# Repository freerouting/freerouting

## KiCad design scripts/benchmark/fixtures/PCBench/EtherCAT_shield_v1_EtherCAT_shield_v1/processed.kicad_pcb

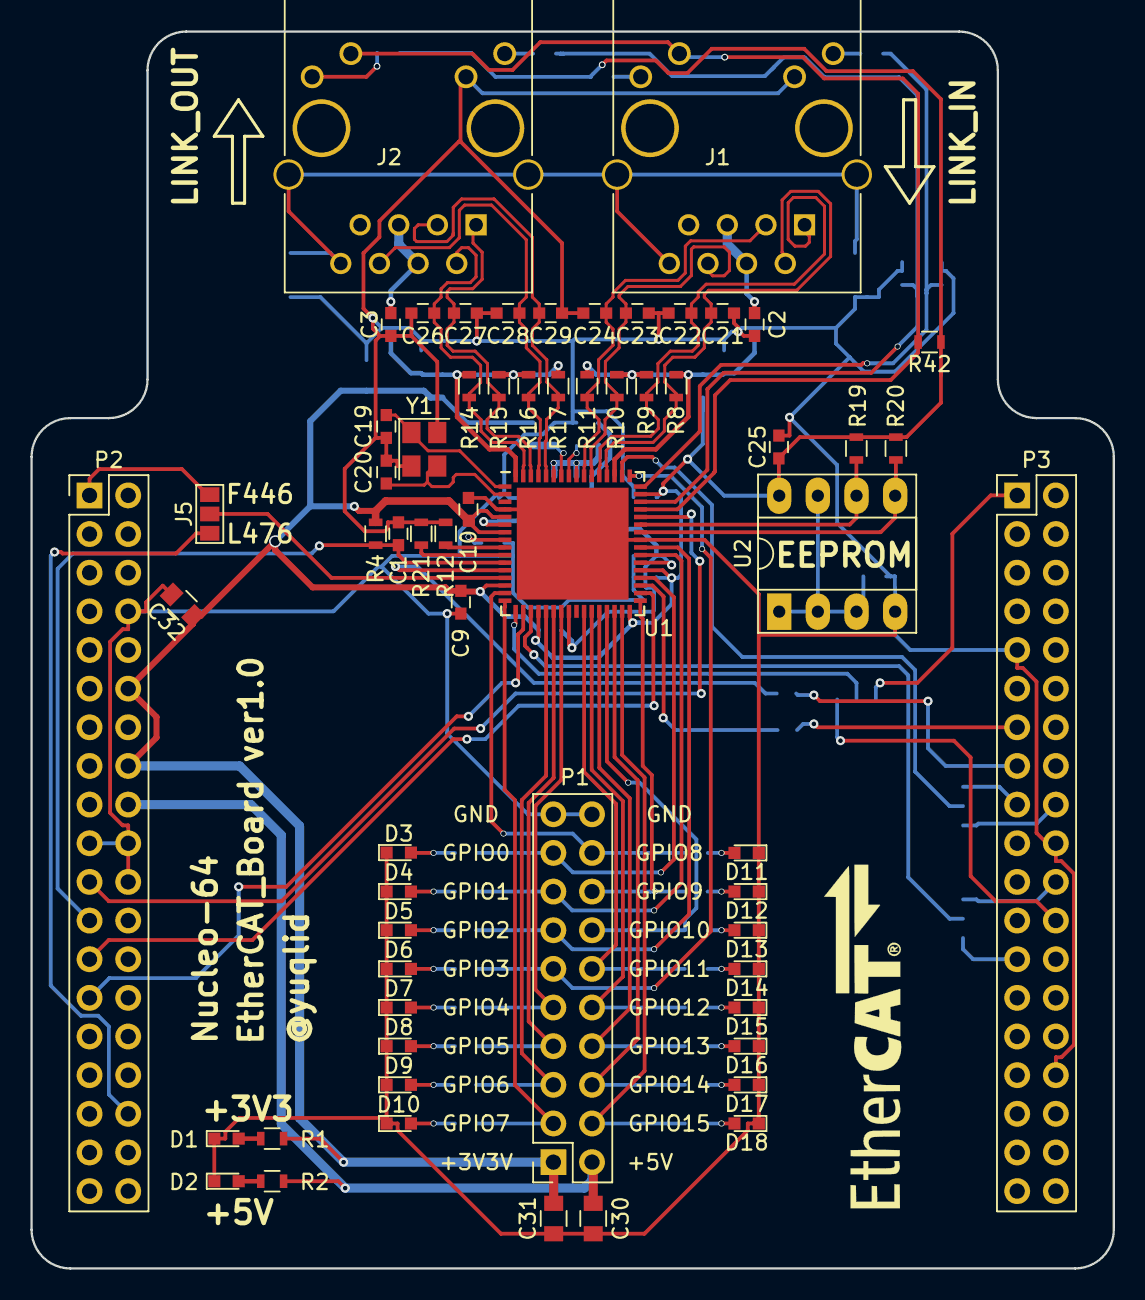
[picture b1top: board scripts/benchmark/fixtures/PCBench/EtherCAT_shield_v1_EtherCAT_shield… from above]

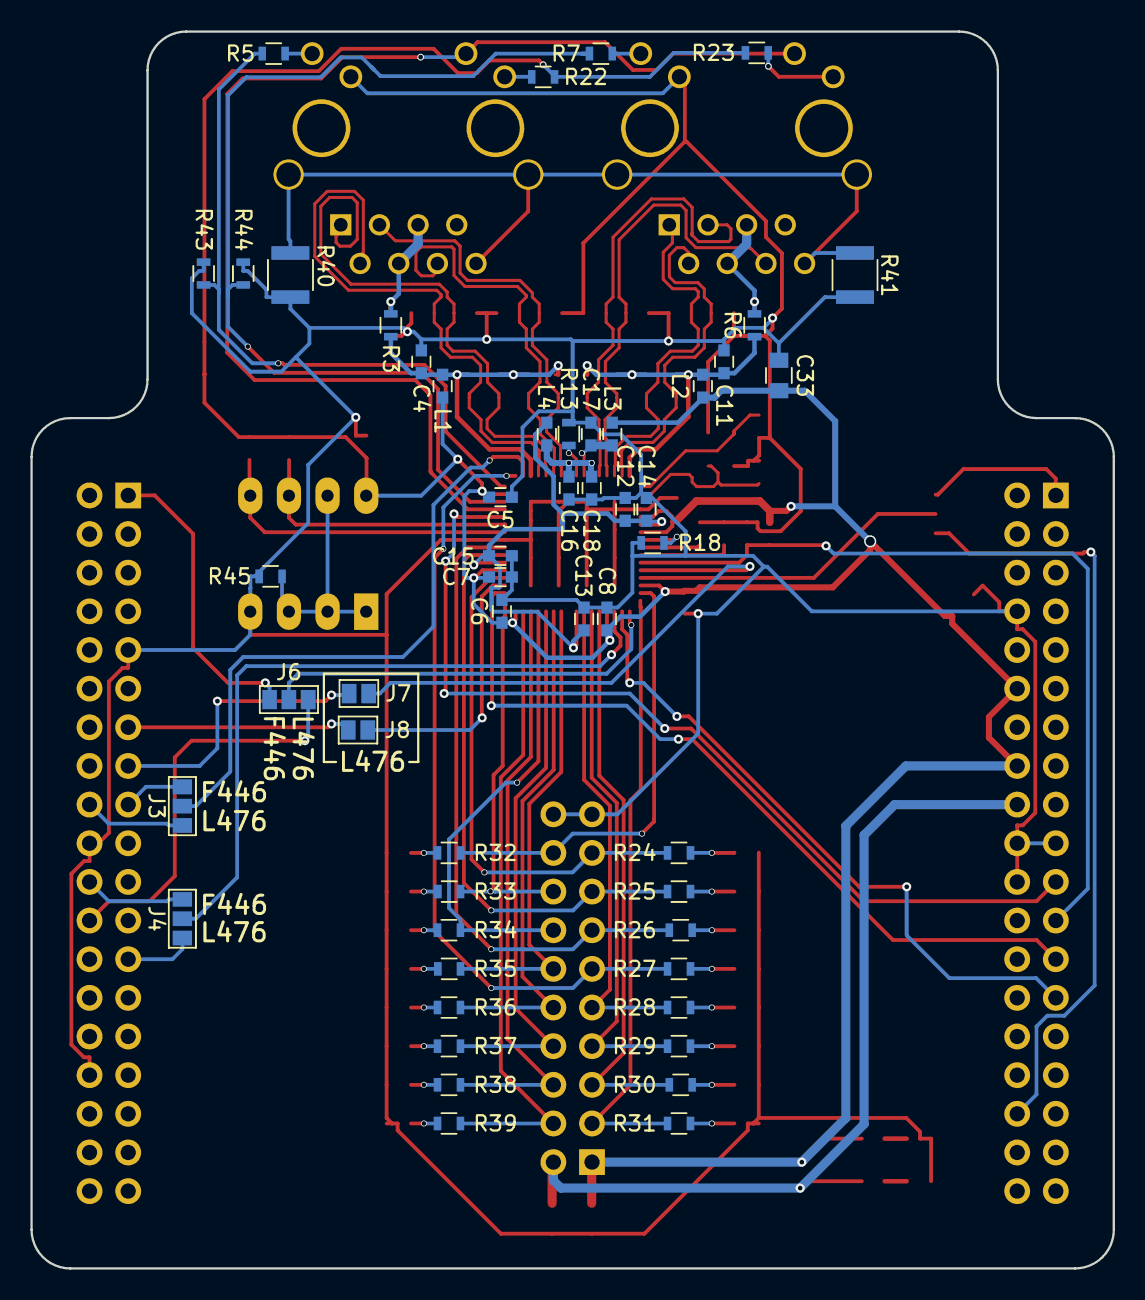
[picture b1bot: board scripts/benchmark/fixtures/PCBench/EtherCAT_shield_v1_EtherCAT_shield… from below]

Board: 2 copper layers, 71.1 x 81.3 mm, 114 parts (52 on the bottom side), 89 nets.

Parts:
C1, C4, C5, C6, C7, C8, C9, C10, C11, C14, C15, C16, C17, C18, C25: 0.1u; C_0603
C2, C3: 0.022u; C_0603
C12: 1u; C_0603
C13: 470p; C_0603
C19, C20: C; C_0603
C21, C22, C23, C24, C26, C27, C28, C29: 10p; C_0603
C30, C31, C32, C33: 10u; C_0805
D1, D2, D3, D4, D5, D6, D7, D8, D9, D10, D11, D12, D13, D14, D15, D16, D17, D18: LED; LED_0603
J1, J2: RJ45-PULSETRANS; RJ45_J0011D21BNL
J3, J4, J5, J6: GS3
J7, J8: GS2
L1, L2, L3, L4: L; C_0603
P1: CONN_02X10; Socket_Strip_Straight_2x10_Pitch2.54mm
P2, P3: CONN_02X19; Pin_Header_Straight_2x19_Pitch2.54mm
R1, R2: R; R_0603
R3, R6: 0; R_0603
R4, R12, R18, R21, R42, R43, R44: 10k; R_0603
R5, R7, R22, R23: 330; R_0603
R8, R9, R10, R11, R14, R15, R16, R17: 49.9; R_0603
R13: 12.1k; R_0603
R19, R20: 2k; R_0603
R24, R25, R26, R27, R28, R29, R30, R31, R32, R33, R34, R35, R36, R37, R38, R39: 1k; R_0603
R40, R41: R; R_1210
R45: 4.7k; R_0603
U1: LAN9252; QFN-64-1EP_9x9mm_Pitch0.5mm
U2: 24LC00; DIP-8_W7.62mm_Socket_LongPads
Y1: Crystal_GND24; Crystal_SMD_Abracon_ABM8G-4pin_3.2x2.5mm

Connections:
+3V3: C5.1, C6.1, C7.1, C8.1, C9.1, C10.1, C25.1, C31.1, C32.1, C33.1, L1.1, L2.1, L3.1, P1.1, P2.12, P2.16, R1.1, R4.1, R19.1, R20.1, R22.1, R23.1, R42.1, U1.5, U1.7, U1.14, U1.20, U1.32, U1.37, U1.47, U2.8
+5V: C30.1, P1.2, P2.18, R2.1
/LAN9252/LINKACTLED0: R5.1, R43.1, U1.48
/LAN9252/LINKACTLED1: R7.1, R44.1, U1.46
/LAN9252/RUNLED: J1.11, J2.11, R42.2, U1.45
/LAN9252/VDD33TXRX1: C4.1, L1.2, R3.2, R8.2, R9.2, R10.2, R11.2, U1.51
/LAN9252/VDDTXRX2: C11.1, L2.2, R6.1, R14.2, R15.2, R16.2, R17.2, U1.64
GND: C1.2, C2.2, C3.2, C4.2, C5.2, C6.2, C7.2, C8.2, C9.2, C10.2, C11.2, C12.2, C13.2, C14.2, C15.2, C16.2, C17.2, C18.2, C19.2, C20.2, C21.2, C22.2, C23.2, C24.2, C25.2, C26.2, C27.2, C28.2, C29.2, C30.2, C31.2, C32.2, C33.2, D1.1, D2.1, D3.1, D4.1, D5.1, D6.1, D7.1, D8.1, D9.1, D10.1, D11.1, D12.1, D13.1, D14.1, D15.1, D16.1, D17.1, D18.1, J1.10, J2.10, P1.19, P1.20, P2.8, P2.19, P2.20, P2.22, P3.9, P3.20, P3.32, R12.2, R13.2, R18.2, R21.2, R40.2, R41.2, R43.2, R44.2, R45.2, U1.4, U1.41, U1.65, U2.4, Y1.2, Y1.4
GNDPWR: J1.8, J1.13, J1.14, J2.8, J2.13, J2.14, R40.1, R41.1
GPIO0: P1.17, R24.2, U1.36
GPIO1: P1.15, R25.2, U1.39
GPIO2: P1.13, R26.2, U1.40
GPIO3: P1.11, R27.2, U1.49
GPIO4: P1.9, R28.2, U1.23
GPIO5: P1.7, R29.2, U1.22
GPIO6: P1.5, R30.2, U1.21
GPIO7: P1.3, R31.2, U1.16
GPIO8: P1.18, R32.2, U1.15
GPIO9: P1.16, R33.2, U1.33
GPIO10: P1.14, R34.2, U1.29
GPIO11: P1.12, R35.2, U1.26
GPIO12: P1.10, R36.2, U1.27
GPIO13: P1.8, R37.2, U1.28
GPIO14: P1.6, R38.2, U1.30
GPIO15: P1.4, R39.2, U1.31
LAN9252_IRQ: P2.21, U1.44
LAN9252_RST: C1.1, P2.23, R4.2, U1.11
unnamed: C2.1, J1.4, J1.5, R3.1
unnamed: C3.1, J2.4, J2.5, R6.2
unnamed: C12.1, C13.1, C14.1, C15.1, L4.1, U1.6, U1.24, U1.38
unnamed: C16.1, C18.1, L4.2, U1.56, U1.59
unnamed: C17.1, L3.2, U1.58
unnamed: C19.1, U1.1, Y1.1
unnamed: C20.1, U1.2, Y1.3
unnamed: D1.2, R1.2
unnamed: D2.2, R2.2
unnamed: D3.2, R24.1
unnamed: D4.2, R25.1
unnamed: D5.2, R26.1
unnamed: D6.2, R27.1
unnamed: D7.2, R28.1
unnamed: D8.2, R29.1
unnamed: D9.2, R30.1
unnamed: D10.2, R31.1
unnamed: D11.2, R32.1
unnamed: D12.2, R33.1
unnamed: D13.2, R34.1
unnamed: D14.2, R35.1
unnamed: D15.2, R36.1
unnamed: D16.2, R37.1
unnamed: D17.2, R38.1
unnamed: D18.2, R39.1
unnamed: J1.9, R5.2
unnamed: J1.12, R22.2
unnamed: J2.9, R7.2
unnamed: J2.12, R23.2
unnamed: R12.1, U1.9
unnamed: R13.1, U1.57
unnamed: R18.1, U1.8
unnamed: R19.2, U1.43, U2.6
unnamed: R20.2, U1.42, U2.5
unnamed: R21.1, U1.10
unnamed: R45.1, U2.1, U2.2, U2.3, U2.7
PA6: J8.2, P3.13
PA7: J7.2, P3.15
PB0: J5.3, P2.34
PB1: J6.3, P3.24
PB2: J4.1, P3.22
PB6: J3.1, P3.17
PB10: J4.3, P3.25
PB11: J3.3, P3.18
PC9: J6.1, P3.1
PC10: J5.1, P2.1
RX1_N: C23.1, J1.6, R10.1, U1.54
RX1_P: C24.1, J1.3, R11.1, U1.55
RX2_N: C28.1, J2.6, R16.1, U1.61
RX2_P: C29.1, J2.3, R17.1, U1.60
SCK: J4.2, U1.19
SIO0: J6.2, U1.17
SIO1: J5.2, U1.13
SIO2: J7.1, U1.12
SIO3: J8.1, U1.35
SYNC0: P2.25, U1.34
SYNC1: P2.27, U1.18
TX1_N: C21.1, J1.2, R8.1, U1.52
TX1_P: C22.1, J1.1, R9.1, U1.53
TX2_N: C26.1, J2.2, R14.1, U1.63
TX2_P: C27.1, J2.1, R15.1, U1.62
~SCS: J3.2, U1.50

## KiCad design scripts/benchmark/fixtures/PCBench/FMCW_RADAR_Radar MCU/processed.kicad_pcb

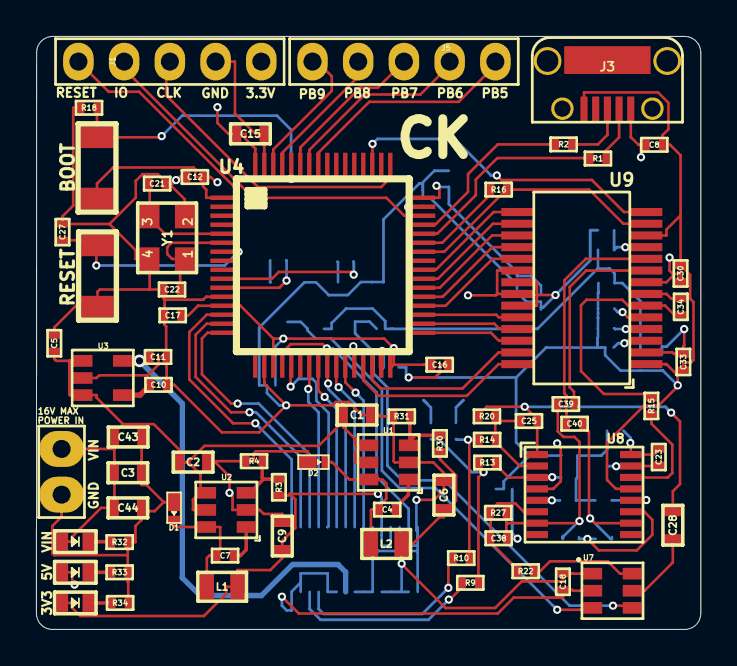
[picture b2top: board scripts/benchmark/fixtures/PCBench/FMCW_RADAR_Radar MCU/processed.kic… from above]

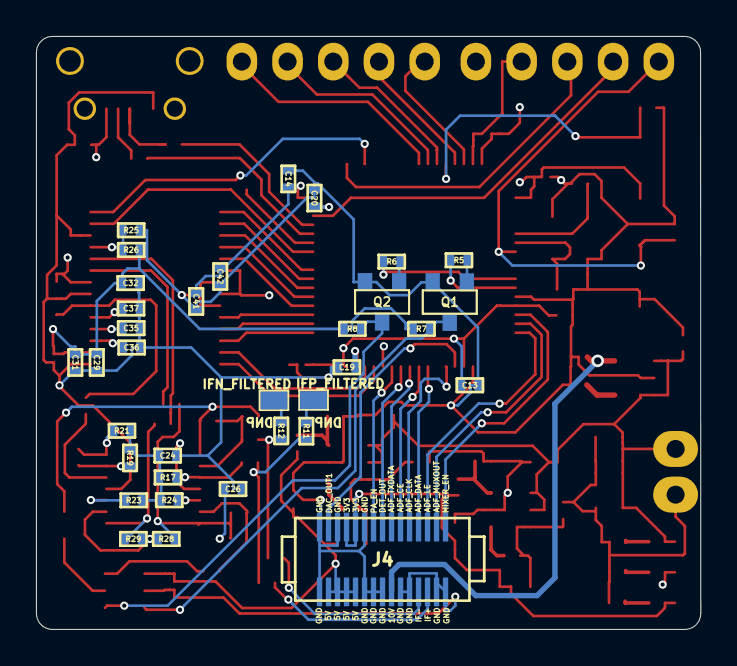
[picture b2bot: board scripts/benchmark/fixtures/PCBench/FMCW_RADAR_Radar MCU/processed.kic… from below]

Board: 4 copper layers, 36.9 x 32.9 mm, 104 parts (34 on the bottom side), 89 nets.

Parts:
3V3, 5V: Led_Diode; Diode_0603
BOOT: DFU_Button; Button_B3U_1000P
C1, C2, C15, C28: 10uF; SMD_0603
C3, C6, C9, C43, C44: 22uF; SMD_0603
C4, C7, C10: 10nF; SMD_0402
C5, C11, C16, C17, C19, C20, C29: 2.2uF; SMD_0402
C8, C12, C13, C14, C18, C23, C24, C26, C27, C30, C31, C34, C35, C36, C37, C41, C42: 100nF; SMD_0402
C21, C22: 15pF; SMD_0402
C25, C38: 33pF; SMD_0402
C32, C33: 100pF; SMD_0402
C39, C40: 1uF; SMD_0402
D1, D2: SDM2U30CSP_7; Diode_SDM2U30CSP_7
IFN_FILTERED: IF-; SolderPad_1_1.5mm_SMD_Rectangle
IFP_FILTERED: IF+; SolderPad_1_1.5mm_SMD_Rectangle
J1: SWD_DEBUGGER; PinHeader_1x5_P2.54mm
J3: USB_MicroB; USB_MicroB_TH
J4: Connector_02x15; PinHeader_2x15_DF12B(5.0)-30DP-0.5V(86)
J5: GPIO_EXTRA; PinHeader_1x5_P2.54mm
L1, L2: 4.7uH; SMD_0805
POWER IN: Connector_01x02; PinHeader_1x2_P2.54mm
Q1, Q2: BSS138; SOT23_3
R1, R2, R16: 22; SMD_0402
R3: 14.7K; SMD_0402
R4, R23, R27, R31: 4.7K; SMD_0402
R5, R6, R22: 100; SMD_0402
R7, R8, R17, R24, R28, R29: 10K; SMD_0402
R9, R10, R26: 0; SMD_0402
R11, R12, R25: DNP; SMD_0402
R13, R14, R18, R20, R32, R33, R34: 1K; SMD_0402
R15, R19: 2.49K; SMD_0402
R21: 49.9; SMD_0402
R30: 24.4K; SMD_0402
RESET: Reset_Button; Button_B3U_1000P
U1, U2: AP3211; SOT23_6
U3: LP2985_10; SOT23_5
U4: STM32F405; LQFP64_10x10mm_P0.5mm
U7: MCP4022_202; SOT23_6
U8: LT1817; SSOP16_3.9x4.9mm_P0.635mm
U9: MAX1426; SSOP28_5.3x10.2mm_P0.65mm
VIN: Led_Diode; Diode_0603
Y1: 8MHz; Crystal_3.2x2.5mm

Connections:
+3V3: 3V3.2, BOOT.2, C9.1, C12.1, C13.1, C14.1, C15.1, C16.1, C17.1, C41.2, C42.2, J1.1, J4.11, J4.12, L1.2, R3.1, U4.1, U4.13, U4.19, U4.32, U4.48, U4.64, U9.20, U9.22
+5V: 5V.2, C6.1, C8.1, C18.1, C26.1, C29.1, C30.1, C31.1, C32.1, C33.1, J3.1, J4.17, J4.18, J4.19, J4.20, L2.2, R7.1, R8.1, R26.2, R30.1, U7.1, U8.4, U9.2, U9.8
+10V: C11.1, J4.24, U3.5
+VBattery: C1.1, C2.1, C3.1, C5.2, C43.1, C44.1, POWER IN.2, U1.4, U1.5, U2.4, U2.5, U3.1, U3.3, VIN.2
ADC_CLK: R16.2, U4.42, U9.13
ADC_IN+: C39.1, U9.9
ADC_IN-: C40.1, U9.10
ADC_OE: U4.51, U9.14
ADF_CE: J4.6, U4.24
ADF_CLK: J4.5, U4.21
ADF_DATA: J4.4, U4.23
ADF_LE: J4.3, U4.16
ADF_MUXOUT: J4.2, U4.15
ADF_TXDATA: J4.7, U4.25
CML: C34.2, R15.1, U9.6
CMLP: R25.1, R26.1, U9.11
CM_BIAS: C24.2, R17.1, R19.2, R21.1, R23.2, R24.1
D0: U4.29, U9.28
D1: U4.30, U9.27
D2: U4.33, U9.26
D3: U4.34, U9.25
D4: U4.35, U9.24
D5: U4.36, U9.19
D6: U4.37, U9.18
D7: U4.38, U9.17
D8: U4.39, U9.16
D9: U4.40, U9.15
DAC_OUT1: J4.14, U4.20
DET_OUT: J4.8, U4.26
GND: C1.2, C2.2, C3.2, C5.1, C6.2, C8.2, C9.2, C10.1, C11.2, C12.2, C13.2, C14.2, C15.2, C16.2, C17.2, C18.2, C19.2, C20.2, C21.2, C22.2, C24.1, C26.2, C27.2, C29.2, C30.2, C31.2, C32.2, C33.2, C34.1, C35.2, C36.2, C37.2, C41.1, C42.1, C43.2, C44.2, D1.2, D2.2, J1.2, J3.5, J4.10, J4.13, J4.15, J4.16, J4.21, J4.22, J4.23, J4.25, J4.26, J4.29, J4.30, POWER IN.1, Q1.2, Q2.2, R4.2, R18.1, R25.2, R31.2, R32.2, R33.2, R34.2, RESET.2, U1.2, U2.2, U3.2, U4.12, U4.18, U4.28, U4.63, U7.2, U8.13, U9.1, U9.7, U9.12, U9.21, U9.23, Y1.2, Y1.4
IFN_Filtered: J4.27, R10.1
IFP_Filtered: J4.28, R9.1
MCP_AOUT: R22.1, U7.6
MCP_CS_3V3: R6.1, U4.10
MCP_UD_3V3: R5.1, U4.11
MCP_WIN: C28.1, U7.5
MCP_~CS~_5V: Q2.3, R8.2, U7.4
MCP_~UD~_5V: Q1.3, R7.2, U7.3
MIXER_ENB: J4.1, U4.14
unnamed: C4.1, U1.1
unnamed: C4.2, D2.1, L2.1, U1.6
unnamed: C7.1, U2.1
unnamed: C7.2, D1.1, L1.1, U2.6
unnamed: C10.2, U3.4
unnamed: C19.1, U4.31
unnamed: C20.1, U4.47
unnamed: C21.1, U4.5, Y1.3
unnamed: C22.1, U4.6, Y1.1
unnamed: C23.1, R21.2, U8.16
unnamed: C23.2, R19.1, U8.15
unnamed: C25.1, C28.2, R20.2, U8.1
unnamed: C25.2, R14.2, R20.1, U8.2
unnamed: C35.1, U9.4
unnamed: C36.1, U9.3
unnamed: C37.1, U9.5
unnamed: C38.1, C39.2, R27.2, R28.1, U8.7
unnamed: C38.2, R22.2, R27.1, U8.6
unnamed: C40.2, R29.2, U8.10
unnamed: R32.1, VIN.1
unnamed: 5V.1, R33.1
unnamed: 3V3.1, R34.1
unnamed: J3.2, R1.1
unnamed: J3.3, R2.1
unnamed: Q1.1, R5.2
unnamed: Q2.1, R6.2
unnamed: R3.2, R4.1, U2.3
unnamed: R10.2, R12.1, R14.1
unnamed: R9.2, R11.1, R13.1
unnamed: IFP_FILTERED.1, R11.2
unnamed: IFN_FILTERED.1, R12.2
unnamed: R13.2, R17.2, U8.3
unnamed: R15.2, U8.14
unnamed: R16.1, U4.43
unnamed: BOOT.1, R18.2, U4.60
unnamed: R23.1, U8.12
unnamed: R24.2, U8.5
unnamed: R28.2, R29.1, U8.11
unnamed: R30.2, R31.1, U1.3
PA_EN: J4.9, U4.27
PB5: J5.1, U4.57
PB6: J5.2, U4.58
PB7: J5.3, U4.59
PB8: J5.4, U4.61
PB9: J5.5, U4.62
RESET: C27.1, J1.5, RESET.1, U4.7
SWDCLK: J1.3, U4.49
SWDIO: J1.4, U4.46
USB_D+: R2.2, U4.45
USB_D-: R1.2, U4.44

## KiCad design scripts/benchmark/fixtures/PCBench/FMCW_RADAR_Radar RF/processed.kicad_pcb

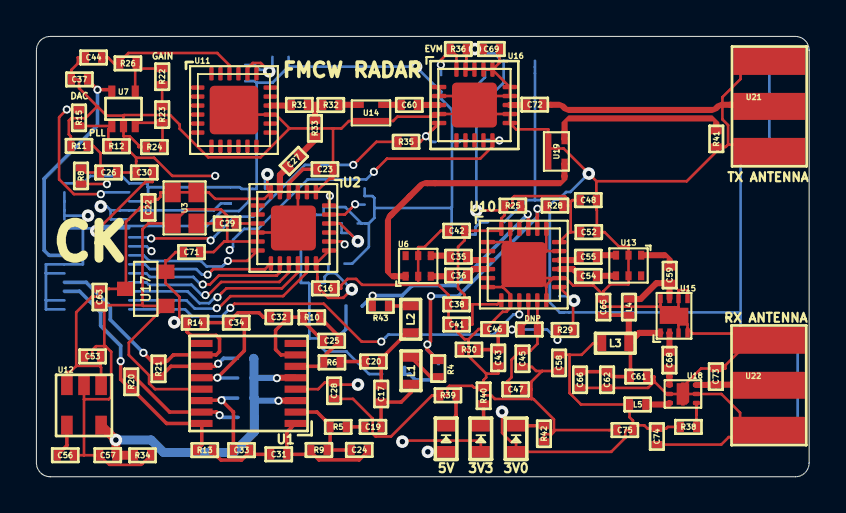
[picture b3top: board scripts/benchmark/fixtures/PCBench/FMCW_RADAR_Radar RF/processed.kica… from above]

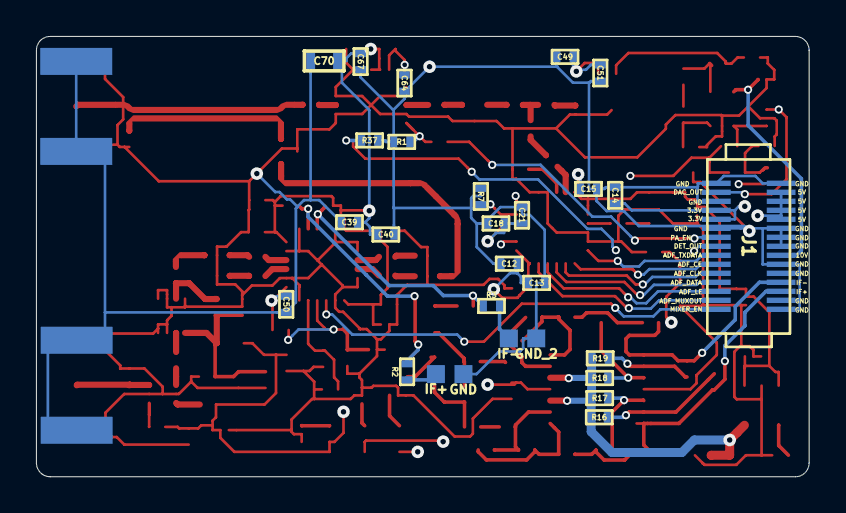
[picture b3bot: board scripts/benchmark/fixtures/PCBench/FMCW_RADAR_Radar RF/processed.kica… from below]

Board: 4 copper layers, 42.9 x 24.5 mm, 143 parts (28 on the bottom side), 92 nets.

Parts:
3V0, 3V3, 5V: Led_Diode; Diode_0603
C12, C13, C14, C21, C22, C28, C37, C38, C39, C40, C43, C45, C46, C48, C50, C51, C52, C53, C64, C67, C69, C74, C75: 100nF; SMD_0402
C15, C16, C18, C59, C68: 18pF; SMD_0402
C17: 2.2nF; SMD_0402
C19, C20, C26: 330nF; SMD_0402
C23, C41, C42, C47, C65: 100pF; SMD_0402
C24, C25, C35, C36, C54, C55, C62: 10pF; SMD_0402
C27: 2pF; SMD_0402
C29, C31, C32, C33, C34, C44: 470pF; SMD_0402
C30, C56, C61: 10nF; SMD_0402
C49, C57, C63, C71: 2.2uF; SMD_0402
C58, C66: DNP; SMD_0402
C60, C72: 1000pF; SMD_0402
C70: 10uF; SMD_0603
C73: 0.5pF; SMD_0402
DNP: DNP; SMD_0402
GND: GND; SolderPad_1_1.5mm_SMD_Rectangle
GND_2: GND; SolderPad_1_1.5mm_SMD_Rectangle
IF+: IF+_PAD; SolderPad_1_1.5mm_SMD_Rectangle
IF-: IF-_PAD; SolderPad_1_1.5mm_SMD_Rectangle
J1: Connector_02x15; PinHeader_2x15_DF12B(5.0)-30DP-0.5V(86)
L1, L2: 2.2uH; SMD_0603
L3: BLM18PG181SN1D; SMD_0603
L4: LQW15AN9N9J80D; SMD_0402
L5: 0.6nH; SMD_0402
R1, R16, R19, R29, R39, R40, R42: 1K; SMD_0402
R2, R3, R15, R30: DNP; SMD_0402
R4, R12, R22, R35, R43: 0; SMD_0402
R5, R6: 549; SMD_0402
R7: 5.49K; SMD_0402
R8: 69.8; SMD_0402
R9, R10, R34: 10K; SMD_0402
R11: 240; SMD_0402
R13, R14: 910; SMD_0402
R17, R18: 130; SMD_0402
R20, R21: 4.99K; SMD_0402
R23, R24, R26: 4.7K; SMD_0402
R25, R28, R41: 50; SMD_0402
R31, R32, R33: 18; SMD_0402
R36: 0 to 27; SMD_0402
R37: 30K; SMD_0402
R38: 100; SMD_0402
U1: LT6232; SSOP16_3.9x4.9mm_P0.635mm
U2: ADF4158; LFCSP24_4x4mm_P0.5mm_1EXP_2.5x2.5mm
U3: SG-210STF; Crystal_2.5x2mm
U4, U9, U23: MITERED_BEND; Mitered_Bend_0.34mm_90
U5: MITERED_BEND; Mitered_Bend_0.34mm_45
U6, U13: 5400BL15B050E; Balun_5400BL15B050E
U7: TLV172; SC70_5
U8: MITERED_BEND; Mitered_Bend_0.34mm_45_Mirrored
U10: ADL5801; LFCSP24_4x4mm_P0.5mm_1EXP_2.5x2.5mm
U11: HMC431LP4; QFN24_4x4mm_P0.5mm_1EXP_2.7x2.7mm
U12: LDS3985; SOT23_5
U14, U19: PAT1220-C-6DB; PAT1220_6dB
U15: TRF37A73; WSON8_2x2mm_P0.5mm_1EXP_0.9x1.6mm
U16: TQP5523; QFN20_4x4mm_P0.5mm_1EXP_2.5x2.5mm
U17: MCP1700; SOT23_3
U18: SKY65404; SKY65404_31
U20: Directional_Coupler; Directional_Coupler_15dB
U21, U22: SMA_Connector

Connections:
25MHz: C29.1, U2.9
+2V5: C57.1, R16.2, R17.2, R18.1, R19.2, R34.1, U1.3, U1.5, U12.5
+3V0: 3V0.2, C49.1, C51.1, C58.1, C71.1, C74.1, C75.1, L3.1, L5.2, R38.1, U11.20, U17.2
+3V3: 3V3.2, C12.1, C13.1, C14.1, C15.1, C16.1, C22.1, C53.1, C63.1, J1.4, J1.5, U2.6, U2.7, U2.8, U2.18, U2.19, U3.1, U3.4, U12.1, U12.3, U17.3
+5V: 5V.2, C18.1, C21.1, C28.2, C38.2, C39.2, C40.2, C41.2, C42.2, C48.2, C50.2, C52.1, C67.2, C69.2, C70.2, J1.26, J1.27, J1.28, J1.29, R25.1, R28.2, R29.1, R36.1, U1.4, U2.22, U10.7, U10.13, U10.18, U10.24, U16.18, U16.19
+10V: C37.1, J1.22, U7.5
ADF_CE: J1.10, U2.13
ADF_CLK: J1.11, U2.14
ADF_DATA: J1.12, U2.15
ADF_LE: J1.13, U2.16
ADF_MUXOUT: J1.14, U2.17
ADF_TXDATA: J1.9, U2.12
DAC_OUT1: J1.2, R15.1
DET_OUT: J1.8, R37.1, U16.10
GND: C12.2, C13.2, C14.2, C15.2, C16.2, C18.2, C21.2, C22.2, C23.2, C28.1, C30.2, C37.2, C38.1, C39.1, C40.1, C41.1, C42.1, C43.1, C44.2, C45.1, C46.1, C47.1, C48.1, C49.2, C50.1, C51.2, C52.2, C53.2, C56.2, C57.2, C58.2, C61.2, C62.2, C63.2, C64.2, C65.2, C66.2, C67.1, C69.1, C70.1, C71.2, C73.2, C74.2, C75.2, GND.1, GND_2.1, J1.1, J1.3, J1.6, J1.16, J1.17, J1.20, J1.21, J1.23, J1.24, J1.25, J1.30, R1.2, R7.2, R11.1, R24.2, R30.2, R34.2, R37.2, R39.2, R40.2, R41.2, R42.2, U1.13, U2.1, U2.2, U2.3, U2.10, U2.11, U2.25, U3.2, U6.2, U6.5, U7.2, U10.1, U10.2, U10.5, U10.6, U10.8, U10.12, U10.14, U10.17, U10.19, U10.23, U10.25, U11.15, U11.25, U12.2, U13.2, U13.5, U14.3, U15.3, U15.4, U15.5, U15.6, U15.8, U15.9, U16.1, U16.2, U16.4, U16.11, U16.12, U16.14, U16.15, U16.16, U16.17, U16.21, U17.1, U18.2, U18.5, U18.7, U19.3, U21.2, U21.3, U21.4, U21.5, U22.2, U22.3, U22.4, U22.5
IF+: R2.1, R4.1, R28.1, U10.20
IF-: R3.2, R25.2, R43.2, U10.21
IFN_Filtered: J1.19, R14.2, R21.1, U1.10
IFP_Filtered: J1.18, R13.1, R20.1, U1.16
MIXER_ENB: J1.15, U10.9
MIXER_LO: U4.2, U6.1
unnamed: C17.1, C19.2, L1.2
unnamed: C17.2, C20.2, L2.2
unnamed: C19.1, R5.1
unnamed: C20.1, R6.1
unnamed: C23.1, U2.4
unnamed: C24.1, C31.2, R9.2, U1.1
unnamed: C24.2, R5.2, R9.1, U1.2
unnamed: C25.1, C32.2, R10.2, U1.7
unnamed: C25.2, R6.2, R10.1, U1.6
unnamed: C26.1, C30.1, R12.1, U2.24
unnamed: C26.2, R8.2, R11.2
unnamed: C27.1, U2.5
unnamed: C27.2, R33.2
unnamed: C29.2, U3.3
unnamed: C31.1, C33.2, R13.2
unnamed: C32.1, C34.2, R14.1
unnamed: C33.1, R17.1, U1.14
unnamed: C34.1, R18.2, U1.12
unnamed: C35.1, U10.3
unnamed: C35.2, U6.4
unnamed: C36.1, U10.4
unnamed: C36.2, U6.3
unnamed: C43.2, C46.2, DNP.2, R29.2, R30.1, U10.10
unnamed: C44.1, R26.1, U11.22
unnamed: C45.2, C47.2, DNP.1, U10.11
unnamed: C54.1, U13.4
unnamed: C55.1, U13.3
unnamed: C56.1, U12.4
unnamed: C59.1, L4.1, U15.7
unnamed: C59.2, U23.1
unnamed: C60.1, U16.3
unnamed: C60.2, U14.2
unnamed: C61.1, C62.1, C65.1, C66.1, L3.2, L4.2, U15.1
unnamed: C64.1, R36.2, U16.20
unnamed: C68.1, U18.4
unnamed: C68.2, U15.2
unnamed: C72.1, U20.1
unnamed: C72.2, U16.13
unnamed: C73.1, U18.3, U22.1
unnamed: 5V.1, R39.1
unnamed: 3V3.1, R40.1
unnamed: 3V0.1, R42.1
unnamed: L1.1, R4.2
unnamed: L2.1, R43.1
unnamed: L5.1, U18.6
unnamed: R1.1, R35.2, U16.5
unnamed: IF+.1, R2.2
unnamed: IF-.1, R3.1
unnamed: R7.1, U2.23
unnamed: R8.1, U2.20
unnamed: R12.2, R15.2, U7.1
unnamed: R16.1, R20.2, U1.15
unnamed: R19.1, R21.2, U1.11
unnamed: R22.1, R26.2, U7.4
unnamed: R22.2, R23.1
unnamed: R23.2, R24.1, U7.3
unnamed: R31.1, U11.16
unnamed: R31.2, R32.2, R33.1
unnamed: R32.1, U14.1
unnamed: R38.2, U18.1
unnamed: R41.1, U20.4
unnamed: U4.1, U8.1
unnamed: U5.1, U9.1
unnamed: U5.2, U8.2
unnamed: U13.1, U23.2
unnamed: U19.1, U20.3
unnamed: U9.2, U19.2
unnamed: U20.2, U21.1
PA_EN: J1.7, R35.1
RFIN: C54.2, U10.15
RFIP: C55.2, U10.16
